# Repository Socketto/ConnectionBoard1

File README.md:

# RS-485 Multi-Socket Board

## Overview

This project describes a **simple RS-485 interface board** designed to allow communication between devices using **different cable types and connectors**.

The board acts as a passive/low-complexity hub, exposing multiple RS-485 connectors while keeping the electrical interface consistent. It is intended for prototyping, testing, field wiring adaptation, and small installations where flexibility is more important than protocol conversion.

## Features

* Multiple connectors for RS-485 communication
* Designed to support **different cable types** on the same board
* Common RS-485 differential bus (A/B)
* Simple and robust hardware design
* No active logic required for basic operation

## Power Distribution

The board includes a **10-pin selector (jumper-based or switch-based, depending on implementation)** that allows flexible routing of the **VCC line**.

Using this selector, VCC can be:

* Routed to one or more RS-485 connectors
* Isolated from specific connectors if required
* Connected to the external power input

This makes it possible to power connected devices directly from the board or keep power lines separated, depending on the application.

## External Power Input

An external power supply can be connected using a **standard 5 mm DC barrel jack**.

* Typical use: powering the RS-485 bus or connected devices
* The external VCC can be selectively distributed via the 10-pin selector
* Ground is shared across all connectors

> ⚠️ **Note:** Ensure that voltage and current ratings are compatible with all connected devices before enabling VCC routing.

## Typical Use Cases

* RS-485 device testing and debugging
* Adapting different connector standards to a single RS-485 bus
* Rapid prototyping of industrial or home automation networks
* Field wiring where multiple cable types must coexist

## Project Status

This is a **simple hardware project**, intended to be easy to understand, modify, and manufacture. It can be extended with:

* Termination resistors
* Biasing resistors
* Protection components (TVS, fuses)
* Optional active transceivers

## License

This project is released under an open-source license. See the `LICENSE` file for details.

---

If you build or modify this board, contributions and improvements are welcome.

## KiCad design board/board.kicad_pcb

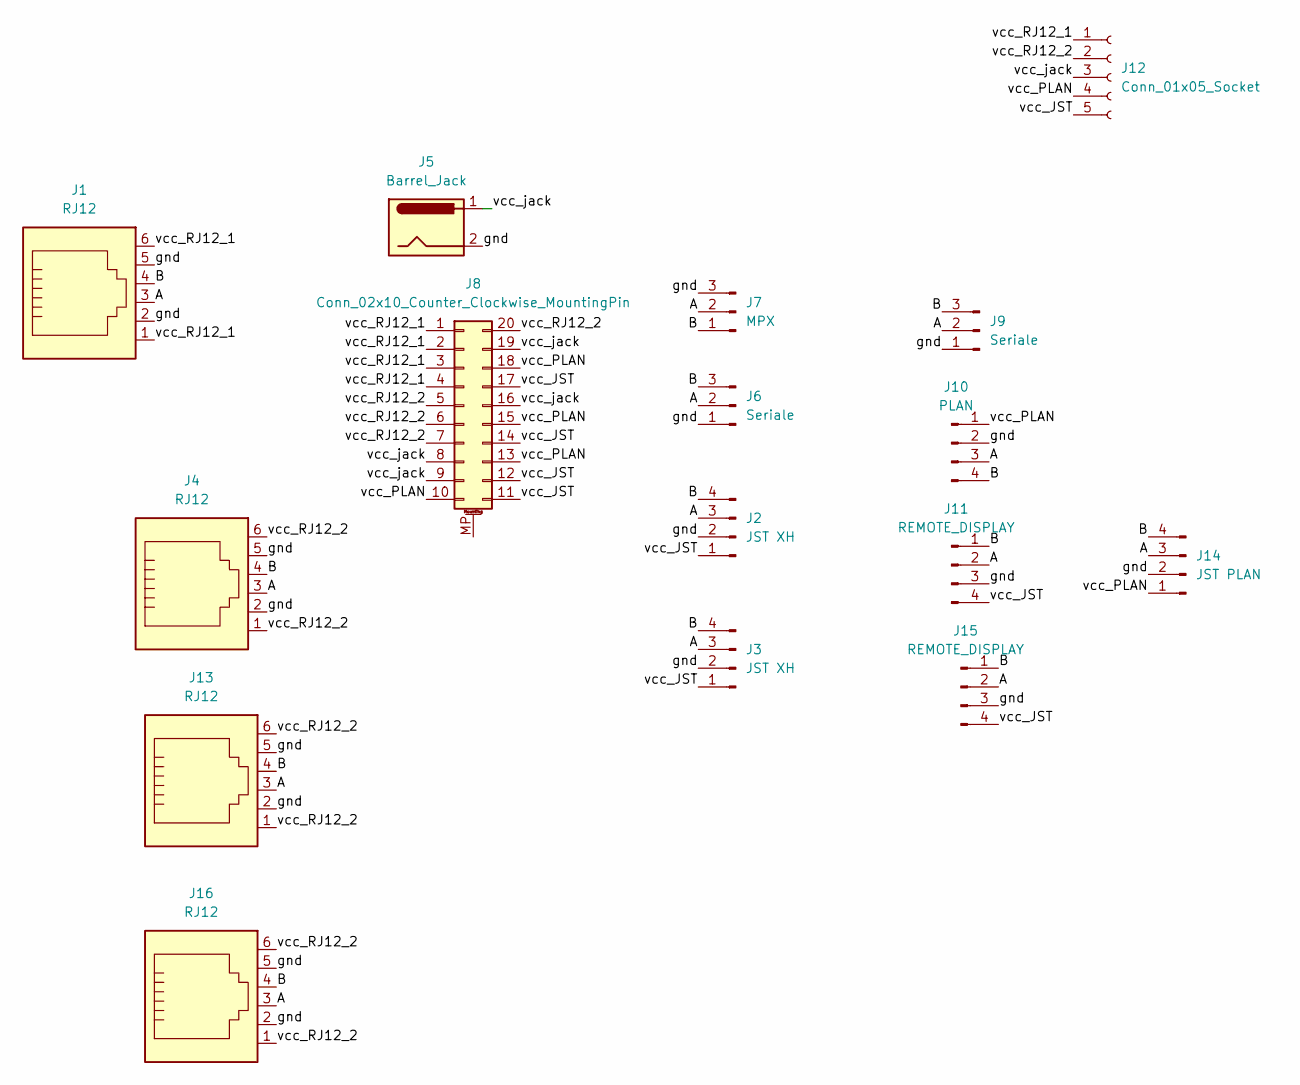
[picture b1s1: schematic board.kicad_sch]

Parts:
J1, J4, J13, J16: RJ12; RJ25_Wayconn_MJEA-660X1_Horizontal
J2, J3: JST XH; JST_XH_B4B-XH-AM_1x04_P2.50mm_Vertical
J5: Barrel_Jack; BarrelJack_GCT_DCJ200-10-A_Horizontal
J6, J9: Seriale; PhoenixContact_MSTBA_2,5_3-G_1x03_P5.00mm_Horizontal
J7: MPX; PhoenixContact_MSTBA_2,5_3-G_1x03_P5.00mm_Horizontal
J8: Conn_02x10_Counter_Clockwise_MountingPin; SW_DIP_SPSTx10_Slide_6.7x26.96mm_W8.61mm_P2.54mm_LowProfile
J10: PLAN; PhoenixContact_MSTBA_2,5_4-G-5,08_1x04_P5.08mm_Horizontal
J11, J15: REMOTE_DISPLAY; 648104131822
J12: Conn_01x05_Socket; TerminalBlock_Phoenix_MPT-0,5-5-2.54_1x05_P2.54mm_Horizontal
J14: JST PLAN; JST_XH_B4B-XH-AM_1x04_P2.50mm_Vertical

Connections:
/A: J1.3, J2.3, J3.3, J4.3, J6.2, J7.2, J9.2, J10.3, J11.2, J13.3, J14.3, J15.2, J16.3
/B: J1.4, J2.4, J3.4, J4.4, J6.3, J7.1, J9.3, J10.4, J11.1, J13.4, J14.4, J15.1, J16.4
/gnd: J1.2, J1.5, J2.2, J3.2, J4.2, J4.5, J5.2, J6.1, J7.3, J9.1, J10.2, J11.3, J13.2, J13.5, J14.2, J15.3, J16.2, J16.5
/vcc_JST: J2.1, J3.1, J8.11, J8.12, J8.14, J8.17, J11.4, J12.5, J15.4
/vcc_PLAN: J8.10, J8.13, J8.15, J8.18, J10.1, J12.4, J14.1
/vcc_RJ12_1: J1.1, J1.6, J8.1, J8.2, J8.3, J8.4, J12.1
/vcc_RJ12_2: J4.1, J4.6, J8.5, J8.6, J8.7, J8.20, J12.2, J13.1, J13.6, J16.1, J16.6
/vcc_jack: J5.1, J8.8, J8.9, J8.16, J8.19, J12.3

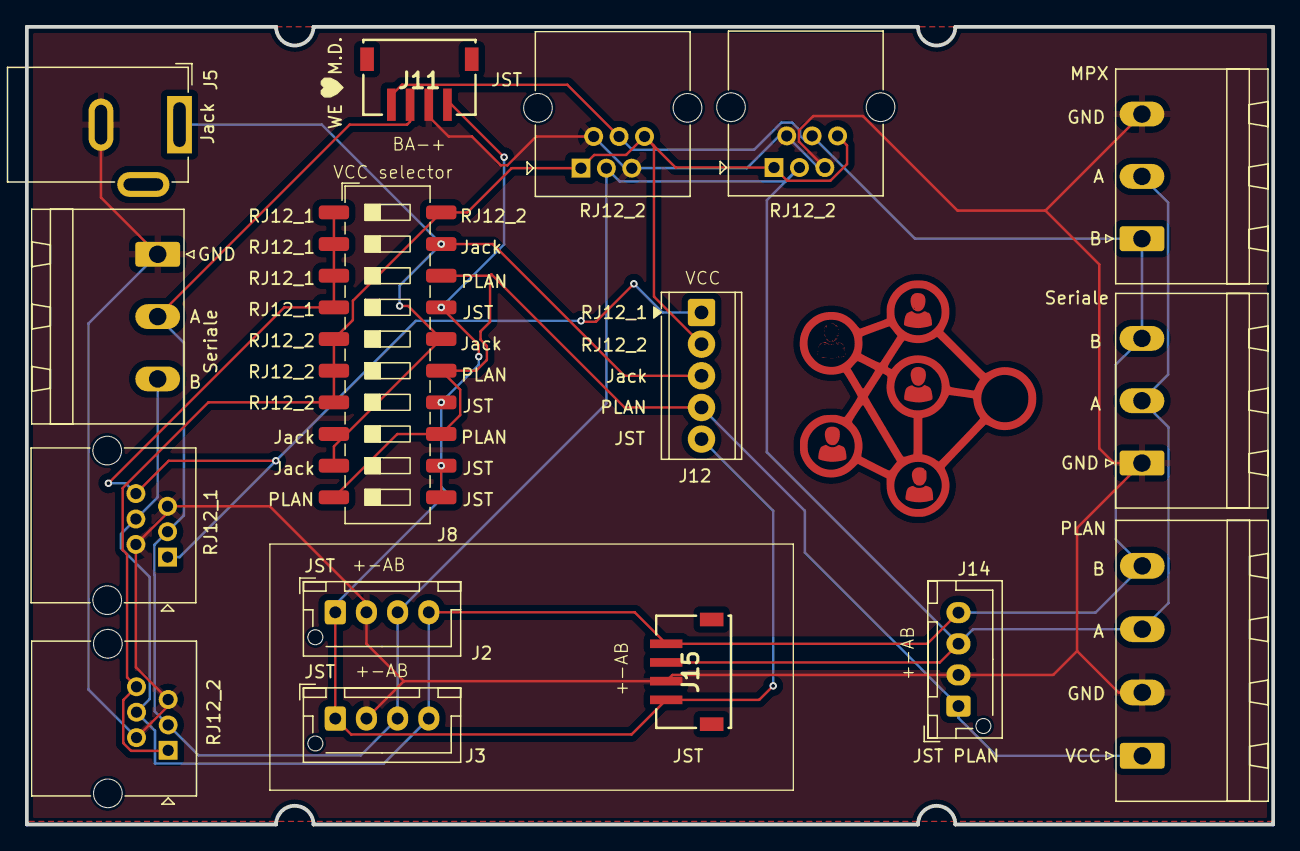
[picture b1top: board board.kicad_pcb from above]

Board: 2 copper layers, 100.0 x 64.0 mm, 16 parts (0 on the bottom side), 8 nets.

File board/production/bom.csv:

Designator,Footprint,Quantity,Value,LCSC Part #
"J1, J13, J16, J4",RJ25_Wayconn_MJEA-660X1_Horizontal,4,RJ12,
J10,"PhoenixContact_MSTBA_2,5_4-G-5,08_1x04_P5.08mm_Horizontal",1,PLAN,
"J11, J15",648104131822,2,REMOTE_DISPLAY,
J12,"TerminalBlock_Phoenix_MPT-0,5-5-2.54_1x05_P2.54mm_Horizontal",1,Conn_01x05_Socket,
J14,JST_XH_B4B-XH-AM_1x04_P2.50mm_Vertical,1,JST PLAN,
"J2, J3",JST_XH_B4B-XH-AM_1x04_P2.50mm_Vertical,2,JST XH,
J5,BarrelJack_GCT_DCJ200-10-A_Horizontal,1,Barrel_Jack,
"J6, J9","PhoenixContact_MSTBA_2,5_3-G_1x03_P5.00mm_Horizontal",2,Seriale,
J7,"PhoenixContact_MSTBA_2,5_3-G_1x03_P5.00mm_Horizontal",1,MPX,
J8,SW_DIP_SPSTx10_Slide_6.7x26.96mm_W8.61mm_P2.54mm_LowProfile,1,Conn_02x10_Counter_Clockwise_MountingPin,

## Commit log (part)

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2026-01-29 [FIX] First commit
2026-01-29 [UPD] Update readme with image of board
2026-01-30 [ADD] Add new sockets
2026-01-30 [UPD] Update image
2026-01-31 [UPD] Final version for JLCPCB
2026-02-18 [ENH] Enhance description
